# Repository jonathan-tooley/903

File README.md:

# 903

u3

GPA7  Trace 3
GPA6  Manual 3
GPA5  Trace 2
GPA4  Manual 2
GPA3  Trace 1
GPA2  Manual 1
GPA1  nc
GPA0  nc

GPB7  IR 1 Led
GPB6  IR 1 SW
GPB5  nc
GPB4  IR 2 Led
GPB3  IR 2 SW
GPB2  nc
GPB1  IR 3 Led
GPB0  IR 3 SW

u4 

GP7 Obey
GP6 Obey
GP5 Enter
GP4 Enter
GP3 Cycle Repeat
GP2 
GP1 Cycle Stop
GP0 Order Stop

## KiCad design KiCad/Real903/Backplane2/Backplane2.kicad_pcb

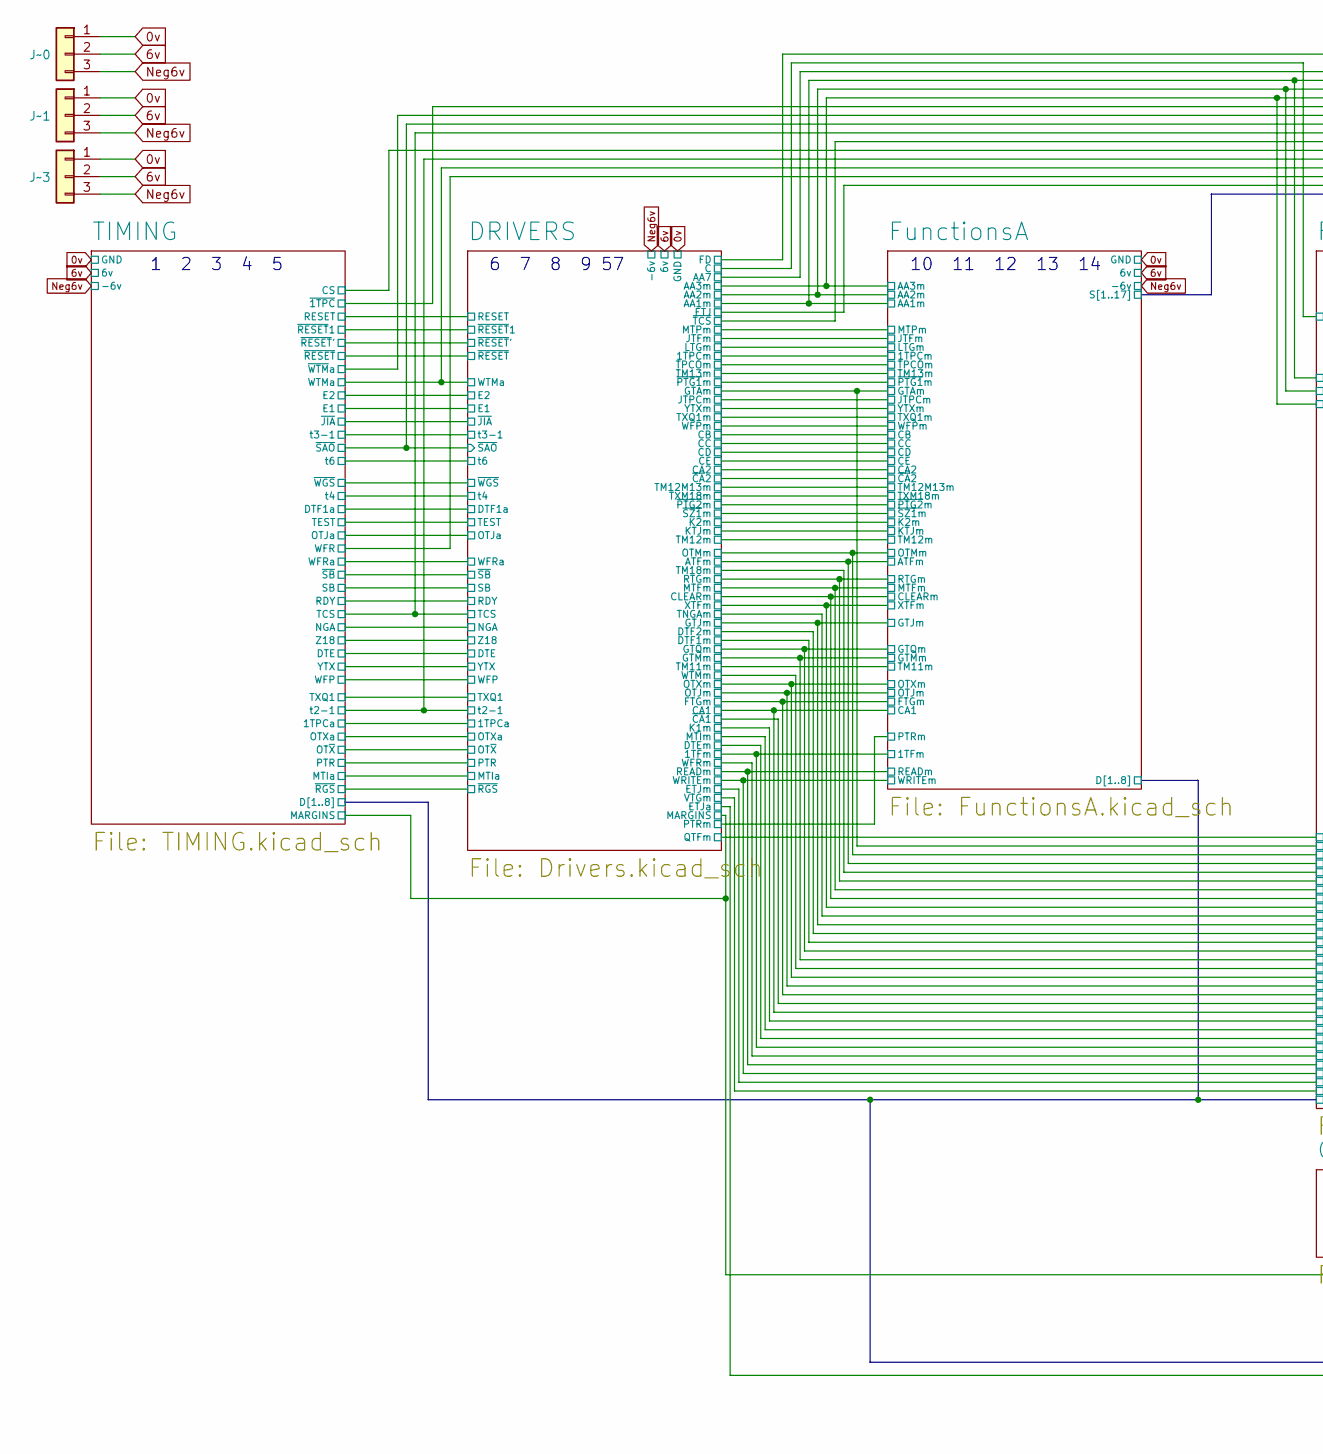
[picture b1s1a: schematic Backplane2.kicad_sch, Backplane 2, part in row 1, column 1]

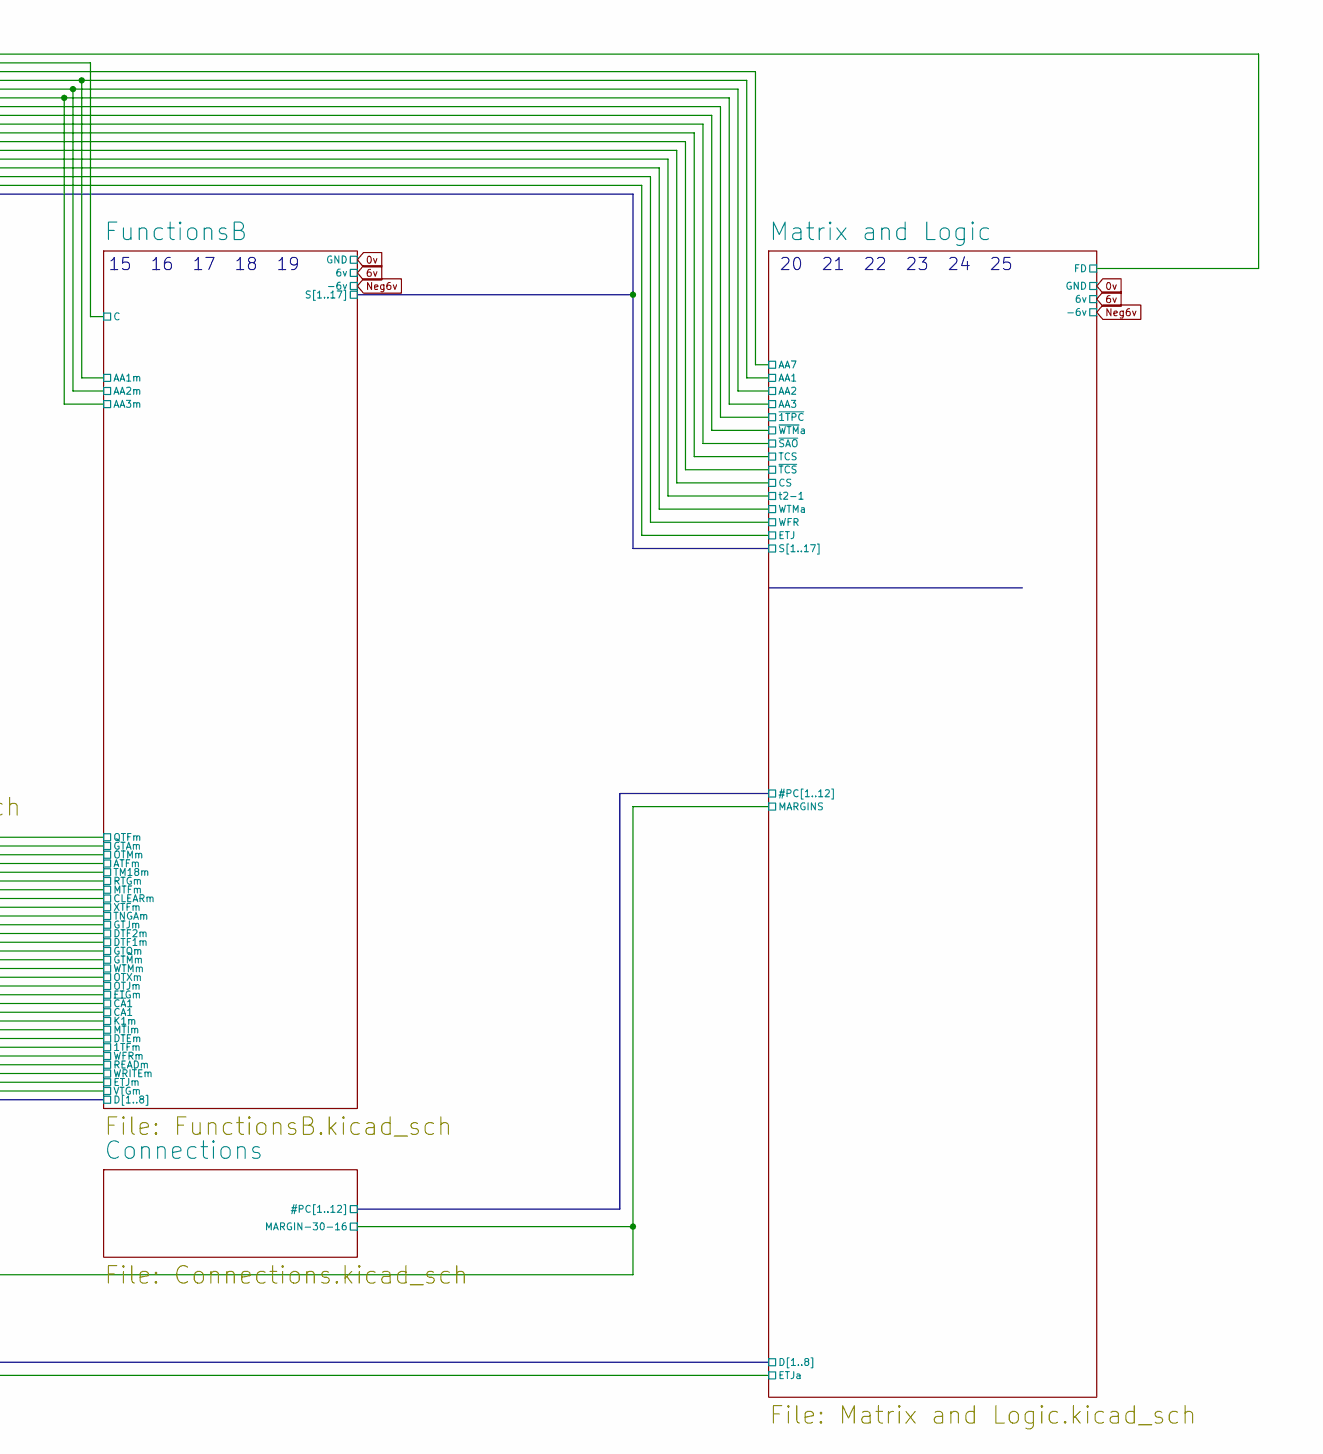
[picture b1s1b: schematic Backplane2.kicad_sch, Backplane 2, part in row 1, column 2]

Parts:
J~0, J~1, J~3: TerminalBlock_5.08_1x03

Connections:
0v: J~0.1, J~1.1, J~3.1; also elsewhere on the board
6v: J~0.2, J~1.2, J~3.2; also elsewhere on the board
Neg6v: J~0.3, J~1.3, J~3.3; also elsewhere on the board

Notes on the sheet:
1 2 3 4 5
6 7 8 9 57
20 21 22 23 24 25
10 11 12 13 14
15 16 17 18 19

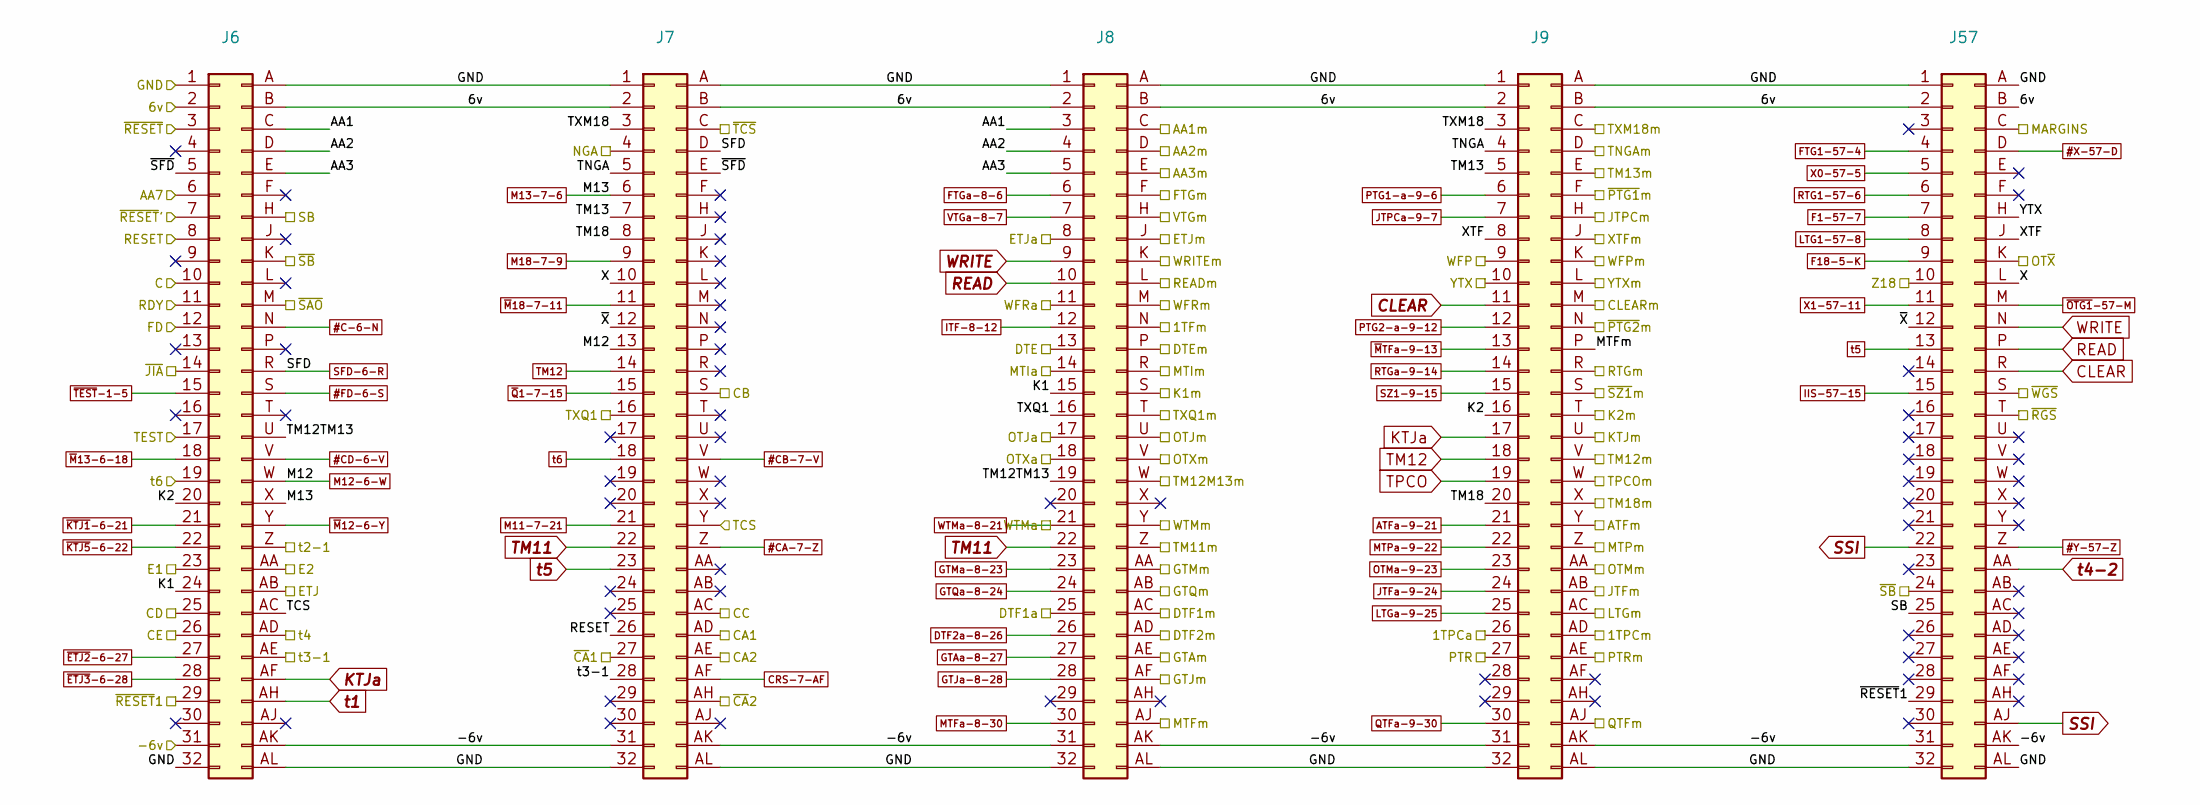
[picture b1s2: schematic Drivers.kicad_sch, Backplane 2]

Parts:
J6, J7, J8, J9, J57: DIN41612_B_2x32_Vertical

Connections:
0v: J6.1, J6.32, J6.A, J6.AL, J7.1, J7.32, J7.A, J7.AL, J8.1, J8.32, J8.A, J8.AL, J9.1, J9.32, J9.A, J9.AL, J57.1, J57.32, J57.A, J57.AL; also elsewhere on the board
6v: J6.2, J6.B, J7.2, J7.B, J8.2, J8.B, J9.2, J9.B, J57.2, J57.B; also elsewhere on the board
#C-6-N: J6.N; also elsewhere on the board
#CA-7-Z: J7.Z; also elsewhere on the board
#CB-7-V: J7.V; also elsewhere on the board
#CD-6-V: J6.V; also elsewhere on the board
#FD-6-S: J6.S; also elsewhere on the board
#X-57-D: J57.D; also elsewhere on the board
#Y-57-Z: J57.Z; also elsewhere on the board
/DRIVERS/1TPCa: J9.26; also elsewhere on the board
/DRIVERS/AA1: J6.C, J8.3
/DRIVERS/AA2: J6.D, J8.4
/DRIVERS/AA3: J6.E, J8.5
/DRIVERS/AA7: J6.6; also elsewhere on the board
/DRIVERS/C: J6.10; also elsewhere on the board
/DRIVERS/CC: J7.AC; also elsewhere on the board
/DRIVERS/CD: J6.25; also elsewhere on the board
/DRIVERS/CE: J6.26; also elsewhere on the board
/DRIVERS/DTE: J8.13; also elsewhere on the board
/DRIVERS/DTEm: J8.P; also elsewhere on the board
/DRIVERS/DTF1a: J8.25; also elsewhere on the board
/DRIVERS/ETJ: J6.AB; also elsewhere on the board
/DRIVERS/ETJa: J8.8; also elsewhere on the board
/DRIVERS/FD: J6.12; also elsewhere on the board
/DRIVERS/JTFm: J9.AB; also elsewhere on the board
/DRIVERS/K1: J6.24, J8.15
/DRIVERS/K2: J6.20, J9.16
/DRIVERS/K2m: J9.T; also elsewhere on the board
/DRIVERS/MTFm: J8.AJ, J9.P; also elsewhere on the board
/DRIVERS/MTIa: J8.14; also elsewhere on the board
/DRIVERS/MTIm: J8.R; also elsewhere on the board
/DRIVERS/NGA: J7.4; also elsewhere on the board
/DRIVERS/OTJa: J8.17; also elsewhere on the board
/DRIVERS/OTXa: J8.18; also elsewhere on the board
/DRIVERS/OT~X: J57.K; also elsewhere on the board
/DRIVERS/PTR: J9.27; also elsewhere on the board
/DRIVERS/PTRm: J9.AE; also elsewhere on the board
/DRIVERS/RDY: J6.11; also elsewhere on the board
/DRIVERS/RESET: J6.8, J7.26; also elsewhere on the board
/DRIVERS/SB: J6.H, J57.25; also elsewhere on the board
/DRIVERS/TCS: J6.AC, J7.Y; also elsewhere on the board
/DRIVERS/TM11m: J8.Z; also elsewhere on the board
/DRIVERS/TM12M13m: J8.W; also elsewhere on the board
/DRIVERS/TM12TM13: J6.U, J8.19
/DRIVERS/TM12m: J9.V; also elsewhere on the board
/DRIVERS/TM13: J7.7, J9.5
/DRIVERS/TM18: J7.8, J9.20
/DRIVERS/TNGA: J7.5, J9.4
/DRIVERS/TNGAm: J9.D; also elsewhere on the board
/DRIVERS/TXM18: J7.3, J9.3
/DRIVERS/TXM18m: J9.C; also elsewhere on the board
/DRIVERS/TXQ1: J7.16, J8.16; also elsewhere on the board
/DRIVERS/TXQ1m: J8.T; also elsewhere on the board
/DRIVERS/WFP: J9.9; also elsewhere on the board
/DRIVERS/WFRa: J8.11; also elsewhere on the board
/DRIVERS/WFRm: J8.M; also elsewhere on the board
/DRIVERS/WTMm: J8.Y; also elsewhere on the board
/DRIVERS/X: J7.10, J57.L
/DRIVERS/XTF: J9.8, J57.J
/DRIVERS/YTX: J9.10, J57.H; also elsewhere on the board
/DRIVERS/Z18: J57.10; also elsewhere on the board
/DRIVERS/t2-1: J6.Z; also elsewhere on the board
/DRIVERS/t3-1: J6.AE, J7.28; also elsewhere on the board
/DRIVERS/~JIA: J6.14; also elsewhere on the board
/DRIVERS/~PTG2m: J9.N; also elsewhere on the board
/DRIVERS/~RESET: J6.3; also elsewhere on the board
/DRIVERS/~RESET1: J6.29, J57.29; also elsewhere on the board
/DRIVERS/~RESET': J6.7; also elsewhere on the board
/DRIVERS/~RGS: J57.T; also elsewhere on the board
/DRIVERS/~SB: J6.K, J57.24; also elsewhere on the board
/DRIVERS/~SFD: J6.5, J7.E
/DRIVERS/~TCS: J7.C; also elsewhere on the board
/DRIVERS/~WGS: J57.S; also elsewhere on the board
/DRIVERS/~X: J7.12, J57.12
/FunctionsA/1TFm: J8.N; also elsewhere on the board
/FunctionsA/1TPCm: J9.AD; also elsewhere on the board
/FunctionsA/AA1m: J8.C; also elsewhere on the board
/FunctionsA/AA2m: J8.D; also elsewhere on the board
/FunctionsA/AA3m: J8.E; also elsewhere on the board
/FunctionsA/ATFm: J9.Y; also elsewhere on the board
/FunctionsA/CA2: J7.AE; also elsewhere on the board
/FunctionsA/CB: J7.S; also elsewhere on the board
/FunctionsA/FTGm: J8.F; also elsewhere on the board
/FunctionsA/GTAm: J8.AE; also elsewhere on the board
/FunctionsA/GTJm: J8.AF; also elsewhere on the board
/FunctionsA/GTQm: J8.AB; also elsewhere on the board
/FunctionsA/JTPCm: J9.H; also elsewhere on the board
/FunctionsA/KTJm: J9.U; also elsewhere on the board
/FunctionsA/LTGm: J9.AC; also elsewhere on the board
/FunctionsA/MTPm: J9.Z; also elsewhere on the board
/FunctionsA/OTJm: J8.U; also elsewhere on the board
/FunctionsA/OTMm: J9.AA; also elsewhere on the board
/FunctionsA/OTXm: J8.V; also elsewhere on the board
/FunctionsA/READm: J8.L; also elsewhere on the board
/FunctionsA/RTGm: J9.R; also elsewhere on the board
/FunctionsA/TM13m: J9.E; also elsewhere on the board
/FunctionsA/TPCOm: J9.W; also elsewhere on the board
/FunctionsA/WFPm: J9.K; also elsewhere on the board
/FunctionsA/WRITEm: J8.K; also elsewhere on the board
/FunctionsA/XTFm: J9.J; also elsewhere on the board
/FunctionsA/YTXm: J9.L; also elsewhere on the board
/FunctionsA/~CA2: J7.AH; also elsewhere on the board
/FunctionsA/~PTG1m: J9.F; also elsewhere on the board
/FunctionsA/~SZ1m: J9.S; also elsewhere on the board
/FunctionsB/CA1: J7.AD; also elsewhere on the board
/FunctionsB/CLEARm: J9.M; also elsewhere on the board
/FunctionsB/DTF1m: J8.AC; also elsewhere on the board
/FunctionsB/DTF2m: J8.AD; also elsewhere on the board
/FunctionsB/ETJm: J8.J; also elsewhere on the board
/FunctionsB/GTMm: J8.AA; also elsewhere on the board
/FunctionsB/K1m: J8.S; also elsewhere on the board
/FunctionsB/QTFm: J9.AJ; also elsewhere on the board
/FunctionsB/TM18m: J9.X; also elsewhere on the board
/FunctionsB/VTGm: J8.H; also elsewhere on the board
/FunctionsB/~CA1: J7.27; also elsewhere on the board
/Matrix and Logic/MARGINS: J57.C; also elsewhere on the board
/TIMING/E1: J6.23; also elsewhere on the board
/TIMING/E2: J6.AA; also elsewhere on the board
/TIMING/TEST: J6.17; also elsewhere on the board
/TIMING/~SAO: J6.M; also elsewhere on the board
ATFa-9-21: J9.21; also elsewhere on the board
CLEAR: J9.11, J57.R
CRS-7-AF: J7.AF; also elsewhere on the board
DTF2a-8-26: J8.26; also elsewhere on the board
F1-57-7: J57.7; also elsewhere on the board
F18-5-K: J57.9; also elsewhere on the board
FTG1-57-4: J57.4; also elsewhere on the board
FTGa-8-6: J8.6; also elsewhere on the board
GTAa-8-27: J8.27; also elsewhere on the board
GTJa-8-28: J8.28; also elsewhere on the board
GTMa-8-23: J8.23; also elsewhere on the board
GTQa-8-24: J8.24; also elsewhere on the board
IIS-57-15: J57.15; also elsewhere on the board
ITF-8-12: J8.12; also elsewhere on the board
JTFa-9-24: J9.24; also elsewhere on the board
JTPCa-9-7: J9.7; also elsewhere on the board
KTJa: J6.AF, J9.17
LTG1-57-8: J57.8; also elsewhere on the board
LTGa-9-25: J9.25; also elsewhere on the board
M11-7-21: J7.21; also elsewhere on the board
M12-6-W: J6.W, J7.13; also elsewhere on the board
M13-7-6: J6.X, J7.6; also elsewhere on the board
M18-7-9: J7.9; also elsewhere on the board
MTFa-8-30: J8.30; also elsewhere on the board
MTPa-9-22: J9.22; also elsewhere on the board
Neg6v: J6.31, J6.AK, J7.31, J7.AK, J8.31, J8.AK, J9.31, J9.AK, J57.31, J57.AK; also elsewhere on the board
OTMa-9-23: J9.23; also elsewhere on the board
PTG1-a-9-6: J9.6; also elsewhere on the board
PTG2-a-9-12: J9.12; also elsewhere on the board
QTFa-9-30: J9.30; also elsewhere on the board
READ: J8.10, J57.P
RTG1-57-6: J57.6; also elsewhere on the board
RTGa-9-14: J9.14; also elsewhere on the board
SFD-6-R: J6.R, J7.D; also elsewhere on the board
SSI: J57.22, J57.AJ
SZ1-9-15: J9.15; also elsewhere on the board
TM11: J7.22, J8.22
TM12: J7.14, J9.18
TPCO: J9.19; also elsewhere on the board
VTGa-8-7: J8.7; also elsewhere on the board
WRITE: J8.9, J57.N
WTMa-8-21: J8.21; also elsewhere on the board
X0-57-5: J57.5; also elsewhere on the board
X1-57-11: J57.11; also elsewhere on the board
t1: J6.AH; also elsewhere on the board
t4-2: J57.AA; also elsewhere on the board
t4-5-26: J6.AD; also elsewhere on the board
t5: J7.23, J57.13
t6: J6.19, J7.18; also elsewhere on the board
~ETJ2-6-27: J6.27; also elsewhere on the board
~ETJ3-6-28: J6.28; also elsewhere on the board
~KTJ1-6-21: J6.21; also elsewhere on the board
~KTJ5-6-22: J6.22; also elsewhere on the board
~M12-6-Y: J6.Y; also elsewhere on the board
~M13-6-18: J6.18; also elsewhere on the board
~M18-7-11: J7.11; also elsewhere on the board
~MTFa-9-13: J9.13; also elsewhere on the board
~OTG1-57-M: J57.M; also elsewhere on the board
~Q1-7-15: J7.15; also elsewhere on the board
~TEST-1-5: J6.15; also elsewhere on the board

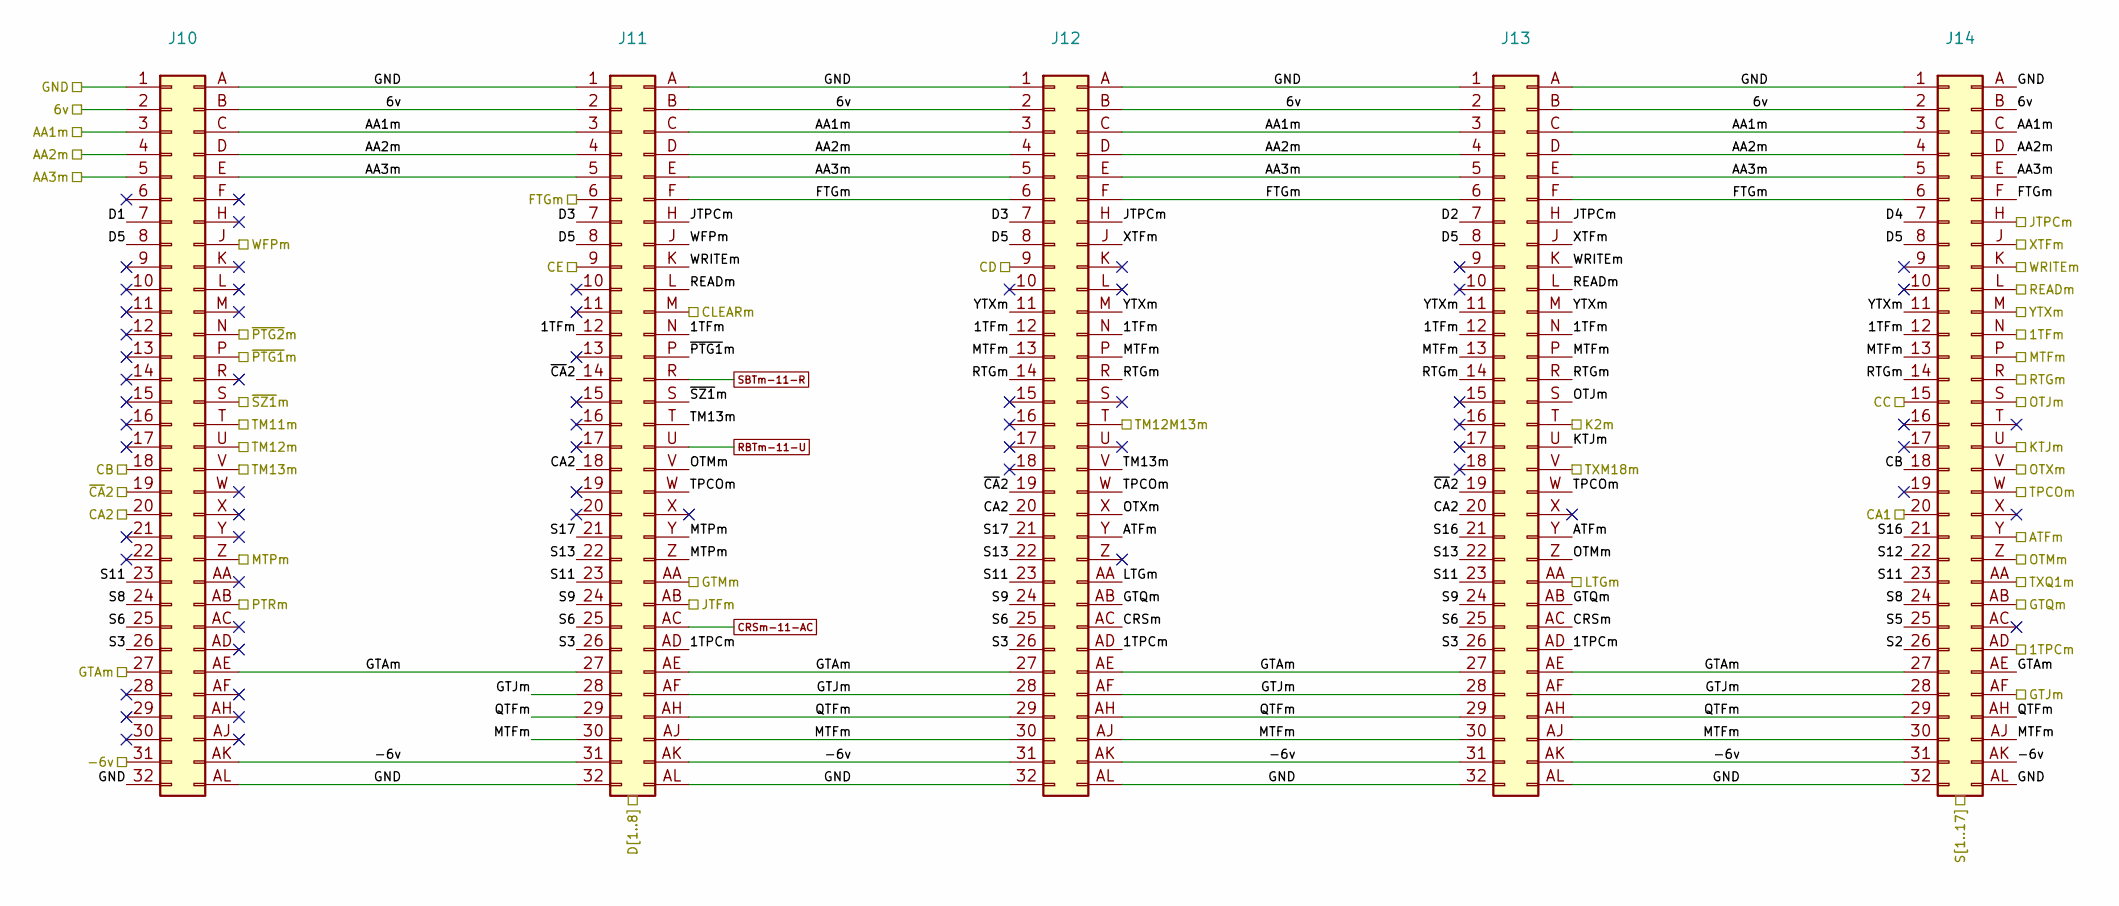
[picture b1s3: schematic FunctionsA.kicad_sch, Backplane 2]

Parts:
J10, J11, J12, J13, J14: DIN41612_B_2x32_Vertical

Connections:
0v: J10.1, J10.32, J10.A, J10.AL, J11.1, J11.32, J11.A, J11.AL, J12.1, J12.32, J12.A, J12.AL, J13.1, J13.32, J13.A, J13.AL, J14.1, J14.32, J14.A, J14.AL; also elsewhere on the board
6v: J10.2, J10.B, J11.2, J11.B, J12.2, J12.B, J13.2, J13.B, J14.2, J14.B; also elsewhere on the board
/DRIVERS/CC: J14.15; also elsewhere on the board
/DRIVERS/CD: J12.9; also elsewhere on the board
/DRIVERS/CE: J11.9; also elsewhere on the board
/DRIVERS/JTFm: J11.AB; also elsewhere on the board
/DRIVERS/K2m: J13.T; also elsewhere on the board
/DRIVERS/MTFm: J11.30, J11.AJ, J12.13, J12.30, J12.AJ, J12.P, J13.13, J13.30, J13.AJ, J13.P, J14.13, J14.30, J14.AJ, J14.P; also elsewhere on the board
/DRIVERS/PTRm: J10.AB; also elsewhere on the board
/DRIVERS/TM11m: J10.T; also elsewhere on the board
/DRIVERS/TM12M13m: J12.T; also elsewhere on the board
/DRIVERS/TM12m: J10.U; also elsewhere on the board
/DRIVERS/TXM18m: J13.V; also elsewhere on the board
/DRIVERS/TXQ1m: J14.AA; also elsewhere on the board
/DRIVERS/~PTG2m: J10.N; also elsewhere on the board
/FunctionsA/1TFm: J11.12, J11.N, J12.12, J12.N, J13.12, J13.N, J14.12, J14.N; also elsewhere on the board
/FunctionsA/1TPCm: J11.AD, J12.AD, J13.AD, J14.AD; also elsewhere on the board
/FunctionsA/AA1m: J10.3, J10.C, J11.3, J11.C, J12.3, J12.C, J13.3, J13.C, J14.3, J14.C; also elsewhere on the board
/FunctionsA/AA2m: J10.4, J10.D, J11.4, J11.D, J12.4, J12.D, J13.4, J13.D, J14.4, J14.D; also elsewhere on the board
/FunctionsA/AA3m: J10.5, J10.E, J11.5, J11.E, J12.5, J12.E, J13.5, J13.E, J14.5, J14.E; also elsewhere on the board
/FunctionsA/ATFm: J12.Y, J13.Y, J14.Y; also elsewhere on the board
/FunctionsA/CA2: J10.20, J11.18, J12.20, J13.20; also elsewhere on the board
/FunctionsA/CB: J10.18, J14.18; also elsewhere on the board
/FunctionsA/CRSm: J12.AC, J13.AC
/FunctionsA/D1: J10.7; also elsewhere on the board
/FunctionsA/D2: J13.7; also elsewhere on the board
/FunctionsA/D3: J11.7, J12.7; also elsewhere on the board
/FunctionsA/D4: J14.7; also elsewhere on the board
/FunctionsA/D5: J10.8, J11.8, J12.8, J13.8, J14.8; also elsewhere on the board
/FunctionsA/FTGm: J11.6, J11.F, J12.6, J12.F, J13.6, J13.F, J14.6, J14.F; also elsewhere on the board
/FunctionsA/GTAm: J10.27, J10.AE, J11.27, J11.AE, J12.27, J12.AE, J13.27, J13.AE, J14.27, J14.AE; also elsewhere on the board
/FunctionsA/GTJm: J11.28, J11.AF, J12.28, J12.AF, J13.28, J13.AF, J14.28, J14.AF; also elsewhere on the board
/FunctionsA/GTQm: J12.AB, J13.AB, J14.AB; also elsewhere on the board
/FunctionsA/JTPCm: J11.H, J12.H, J13.H, J14.H; also elsewhere on the board
/FunctionsA/KTJm: J13.U, J14.U; also elsewhere on the board
/FunctionsA/LTGm: J12.AA, J13.AA; also elsewhere on the board
/FunctionsA/MTPm: J10.Z, J11.Y, J11.Z; also elsewhere on the board
/FunctionsA/OTJm: J13.S, J14.S; also elsewhere on the board
/FunctionsA/OTMm: J11.V, J13.Z, J14.Z; also elsewhere on the board
/FunctionsA/OTXm: J12.X, J14.V; also elsewhere on the board
/FunctionsA/QTFm: J11.29, J11.AH, J12.29, J12.AH, J13.29, J13.AH, J14.29, J14.AH
/FunctionsA/READm: J11.L, J13.L, J14.L; also elsewhere on the board
/FunctionsA/RTGm: J12.14, J12.R, J13.14, J13.R, J14.14, J14.R; also elsewhere on the board
/FunctionsA/S2: J14.26; also elsewhere on the board
/FunctionsA/S3: J10.26, J11.26, J12.26, J13.26; also elsewhere on the board
/FunctionsA/S5: J14.25; also elsewhere on the board
/FunctionsA/S6: J10.25, J11.25, J12.25, J13.25; also elsewhere on the board
/FunctionsA/S8: J10.24, J14.24; also elsewhere on the board
/FunctionsA/S9: J11.24, J12.24, J13.24; also elsewhere on the board
/FunctionsA/S11: J10.23, J11.23, J12.23, J13.23, J14.23; also elsewhere on the board
/FunctionsA/S12: J14.22; also elsewhere on the board
/FunctionsA/S13: J11.22, J12.22, J13.22; also elsewhere on the board
/FunctionsA/S16: J13.21, J14.21; also elsewhere on the board
/FunctionsA/S17: J11.21, J12.21; also elsewhere on the board
/FunctionsA/TM13m: J10.V, J11.T, J12.V; also elsewhere on the board
/FunctionsA/TPCOm: J11.W, J12.W, J13.W, J14.W; also elsewhere on the board
/FunctionsA/WFPm: J10.J, J11.J; also elsewhere on the board
/FunctionsA/WRITEm: J11.K, J13.K, J14.K; also elsewhere on the board
/FunctionsA/XTFm: J12.J, J13.J, J14.J; also elsewhere on the board
/FunctionsA/YTXm: J12.11, J12.M, J13.11, J13.M, J14.11, J14.M; also elsewhere on the board
/FunctionsA/~CA2: J10.19, J11.14, J12.19, J13.19; also elsewhere on the board
/FunctionsA/~PTG1m: J10.P, J11.P; also elsewhere on the board
/FunctionsA/~SZ1m: J10.S, J11.S; also elsewhere on the board
/FunctionsB/CA1: J14.20; also elsewhere on the board
/FunctionsB/CLEARm: J11.M; also elsewhere on the board
/FunctionsB/GTMm: J11.AA; also elsewhere on the board
CRSm-11-AC: J11.AC; also elsewhere on the board
Neg6v: J10.31, J10.AK, J11.31, J11.AK, J12.31, J12.AK, J13.31, J13.AK, J14.31, J14.AK; also elsewhere on the board
RBTm-11-U: J11.U; also elsewhere on the board
SBTm-11-R: J11.R; also elsewhere on the board

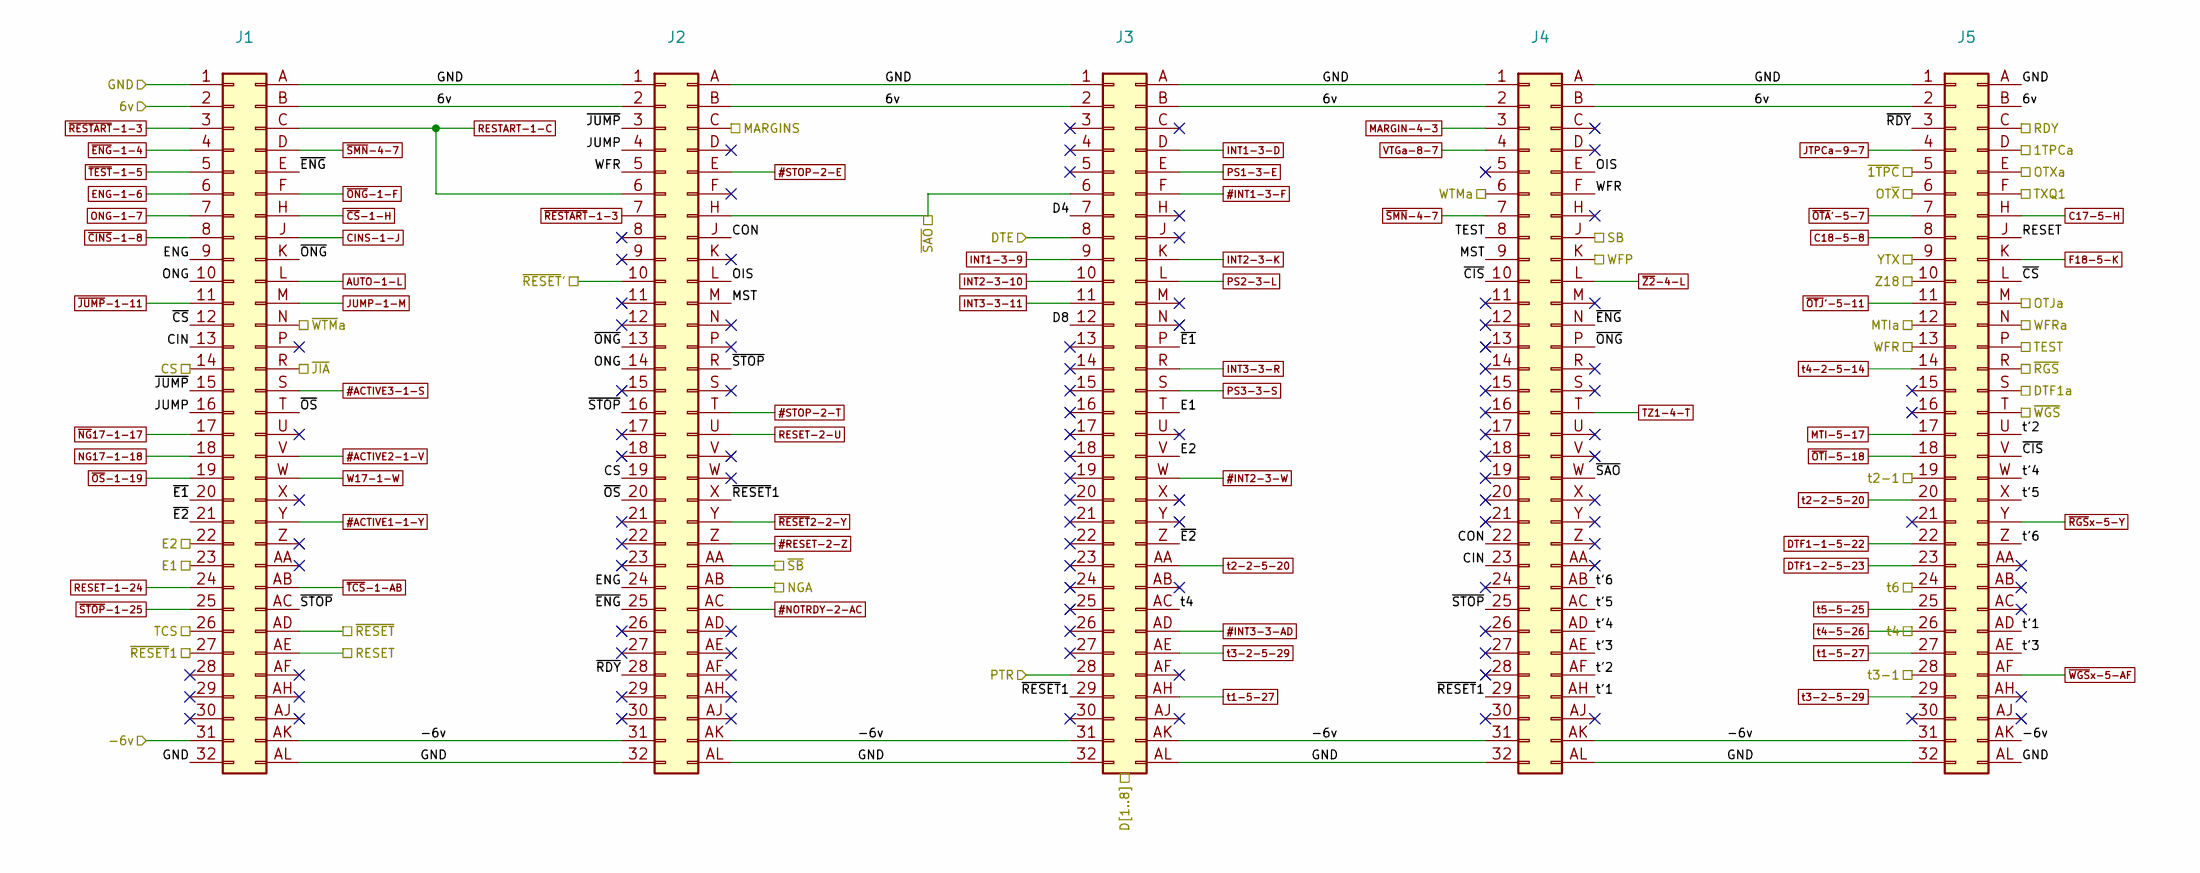
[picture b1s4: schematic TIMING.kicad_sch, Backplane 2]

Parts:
J1, J2, J3, J4, J5: DIN41612_B_2x32_Vertical

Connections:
0v: J1.1, J1.32, J1.A, J1.AL, J2.1, J2.32, J2.A, J2.AL, J3.1, J3.32, J3.A, J3.AL, J4.1, J4.32, J4.A, J4.AL, J5.1, J5.32, J5.A, J5.AL; also elsewhere on the board
6v: J1.2, J1.B, J2.2, J2.B, J3.2, J3.B, J4.2, J4.B, J5.2, J5.B; also elsewhere on the board
#ACTIVE1-1-Y: J1.Y; also elsewhere on the board
#ACTIVE2-1-V: J1.V; also elsewhere on the board
#ACTIVE3-1-S: J1.S; also elsewhere on the board
#INT1-3-F: J3.F; also elsewhere on the board
#INT2-3-W: J3.W; also elsewhere on the board
#INT3-3-AD: J3.AD; also elsewhere on the board
#NOTRDY-2-AC: J2.AC; also elsewhere on the board
#RESET-2-Z: J2.Z; also elsewhere on the board
#STOP-2-E: J2.E; also elsewhere on the board
#STOP-2-T: J2.T; also elsewhere on the board
/DRIVERS/1TPCa: J5.D; also elsewhere on the board
/DRIVERS/DTE: J3.8; also elsewhere on the board
/DRIVERS/DTF1a: J5.S; also elsewhere on the board
/DRIVERS/MTIa: J5.12; also elsewhere on the board
/DRIVERS/NGA: J2.AB; also elsewhere on the board
/DRIVERS/OTJa: J5.M; also elsewhere on the board
/DRIVERS/OTXa: J5.E; also elsewhere on the board
/DRIVERS/OT~X: J5.6; also elsewhere on the board
/DRIVERS/PTR: J3.28; also elsewhere on the board
/DRIVERS/RDY: J5.C; also elsewhere on the board
/DRIVERS/RESET: J1.AE, J5.J; also elsewhere on the board
/DRIVERS/SB: J4.J; also elsewhere on the board
/DRIVERS/TCS: J1.26; also elsewhere on the board
/DRIVERS/TXQ1: J5.F; also elsewhere on the board
/DRIVERS/WFP: J4.K; also elsewhere on the board
/DRIVERS/WFRa: J5.N; also elsewhere on the board
/DRIVERS/YTX: J5.9; also elsewhere on the board
/DRIVERS/Z18: J5.10; also elsewhere on the board
/DRIVERS/t2-1: J5.19; also elsewhere on the board
/DRIVERS/t3-1: J5.28; also elsewhere on the board
/DRIVERS/~JIA: J1.R; also elsewhere on the board
/DRIVERS/~RESET: J1.AD; also elsewhere on the board
/DRIVERS/~RESET1: J1.27, J2.X, J3.29, J4.29; also elsewhere on the board
/DRIVERS/~RESET': J2.10; also elsewhere on the board
/DRIVERS/~RGS: J5.R; also elsewhere on the board
/DRIVERS/~SB: J2.AA; also elsewhere on the board
/DRIVERS/~WGS: J5.T; also elsewhere on the board
/FunctionsA/D4: J3.7; also elsewhere on the board
/FunctionsA/D8: J3.12; also elsewhere on the board
/Matrix and Logic/MARGINS: J2.C; also elsewhere on the board
/Matrix and Logic/WFR: J2.5, J4.F, J5.13; also elsewhere on the board
/Matrix and Logic/~1TPC: J5.5; also elsewhere on the board
/Matrix and Logic/~WTMa: J1.N; also elsewhere on the board
/TIMING/CIN: J1.13, J4.23
/TIMING/CON: J2.J, J4.22
/TIMING/CS: J1.14, J2.19; also elsewhere on the board
/TIMING/E1: J1.23, J3.T; also elsewhere on the board
/TIMING/E2: J1.22, J3.V; also elsewhere on the board
/TIMING/ENG: J1.9, J2.24
/TIMING/JUMP: J1.16, J2.4
/TIMING/MST: J2.M, J4.9
/TIMING/OIS: J2.L, J4.E
/TIMING/ONG: J1.10, J2.14
/TIMING/TEST: J4.8, J5.P; also elsewhere on the board
/TIMING/t'1: J4.AH, J5.AD
/TIMING/t'2: J4.AF, J5.U
/TIMING/t'3: J4.AE, J5.AE
/TIMING/t'4: J4.AD, J5.W
/TIMING/t'5: J4.AC, J5.X
/TIMING/t'6: J4.AB, J5.Z
/TIMING/~CIS: J4.10, J5.V
/TIMING/~CS: J1.12, J5.L
/TIMING/~E1: J1.20, J3.P
/TIMING/~E2: J1.21, J3.Z
/TIMING/~ENG: J1.E, J2.25, J4.N
/TIMING/~JUMP: J1.15, J2.3
/TIMING/~ONG: J1.K, J2.13, J4.P
/TIMING/~OS: J1.T, J2.20
/TIMING/~RDY: J2.28, J5.3
/TIMING/~SAO: J2.H, J3.6, J4.W; also elsewhere on the board
/TIMING/~STOP: J1.AC, J2.16, J2.R, J4.25
AUTO-1-L: J1.L; also elsewhere on the board
C17-5-H: J5.H; also elsewhere on the board
C18-5-8: J5.8; also elsewhere on the board
CINS-1-J: J1.J; also elsewhere on the board
DTF1-1-5-22: J5.22; also elsewhere on the board
DTF1-2-5-23: J5.23; also elsewhere on the board
ENG-1-6: J1.6; also elsewhere on the board
F18-5-K: J5.K; also elsewhere on the board
INT1-3-9: J3.9; also elsewhere on the board
INT1-3-D: J3.D; also elsewhere on the board
INT2-3-10: J3.10; also elsewhere on the board
INT2-3-K: J3.K; also elsewhere on the board
INT3-3-11: J3.11; also elsewhere on the board
INT3-3-R: J3.R; also elsewhere on the board
JTPCa-9-7: J5.4; also elsewhere on the board
JUMP-1-M: J1.M; also elsewhere on the board
MARGIN-4-3: J4.3; also elsewhere on the board
MTI-5-17: J5.17; also elsewhere on the board
NG17-1-18: J1.18; also elsewhere on the board
Neg6v: J1.31, J1.AK, J2.31, J2.AK, J3.31, J3.AK, J4.31, J4.AK, J5.31, J5.AK; also elsewhere on the board
ONG-1-7: J1.7; also elsewhere on the board
PS1-3-E: J3.E; also elsewhere on the board
PS2-3-L: J3.L; also elsewhere on the board
PS3-3-S: J3.S; also elsewhere on the board
RESET-1-24: J1.24; also elsewhere on the board
RESET-2-U: J2.U; also elsewhere on the board
RESTART-1-C: J1.C, J2.6; also elsewhere on the board
TZ1-4-T: J4.T; also elsewhere on the board
VTGa-8-7: J4.4; also elsewhere on the board
W17-1-W: J1.W; also elsewhere on the board
WTMa-8-21: J4.6; also elsewhere on the board
t1-5-27: J3.AH, J5.27; also elsewhere on the board
t2-2-5-20: J3.AA, J5.20; also elsewhere on the board
t3-2-5-29: J3.AE, J5.29; also elsewhere on the board
t4-2-5-14: J5.14; also elsewhere on the board
t4-5-26: J3.AC, J5.26; also elsewhere on the board
t5-5-25: J5.25; also elsewhere on the board
t6: J5.24; also elsewhere on the board
~CINS-1-8: J1.8; also elsewhere on the board
~CS-1-H: J1.H; also elsewhere on the board
~ENG-1-4: J1.4; also elsewhere on the board
~JUMP-1-11: J1.11; also elsewhere on the board
~NG17-1-17: J1.17; also elsewhere on the board
~ONG-1-F: J1.F; also elsewhere on the board
~OS-1-19: J1.19; also elsewhere on the board
~OTA'-5-7: J5.7; also elsewhere on the board
~OTI-5-18: J5.18; also elsewhere on the board
~OTJ'-5-11: J5.11; also elsewhere on the board
~RESET2-2-Y: J2.Y; also elsewhere on the board
~RESTART-1-3: J1.3, J2.7; also elsewhere on the board
~RGSx-5-Y: J5.Y; also elsewhere on the board
~SMN-4-7: J1.D, J4.7; also elsewhere on the board
~STOP-1-25: J1.25; also elsewhere on the board
~TCS-1-AB: J1.AB; also elsewhere on the board
~TEST-1-5: J1.5; also elsewhere on the board
~WGSx-5-AF: J5.AF; also elsewhere on the board
~Z2-4-L: J4.L; also elsewhere on the board
